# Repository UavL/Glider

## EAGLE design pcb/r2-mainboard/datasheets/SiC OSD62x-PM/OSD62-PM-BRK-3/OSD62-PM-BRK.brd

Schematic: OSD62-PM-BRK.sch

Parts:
C1, C2, C3, C6, C7, C8, C9, C10, C11, C12, C13, C14, C15, C17, C18, C19, C20, C61: 0.1uF; C0201; VOLTAGE 6.3V
C4, C62, C63: 1uF; C0402; VOLTAGE 6.3V
C5, C60: 4.7uF; C0402; VOLTAGE 10V
C16, C38, C39, C40, C42, C43, C44, C45, C51: 10uF; C0402; VOLTAGE 10V
C21, C22, C23, C41: 2.2uF; C0402; VOLTAGE 10V
C24, C26, C29, C34, C35, C36, C46, C50, C54, C55, C58: 0.1uF; C0402; VOLTAGE 6.3V
C25: 220uF; B/3528-21R
C27, C31, C32, C33, C37, C57: 10uF; C0603; VOLTAGE 10V
C28: DNP; C0402
C30: 120pF; C0402; VOLTAGE 10V
C47, C49, C53: 47uF; C0603; VOLTAGE 6.3V
C48, C52: 22uF; C0402; VOLTAGE 10V
C56: 47uF; C0805; VOLTAGE 10V
C59: 1nF; C0402; VOLTAGE 6.3V
D1: RED; EIA-STD
D2, D3, D4, D5: GREEN; EIA-STD
D6, D7: RB520S30T1G
D8: RBS2MM40C; SOD-123FL
FUD1, FUD2, FUD3, FUD4, FUD5, FUD6: FIDUCIAL; FIDUCIAL_40MIL
J1: PINHD-1X21.27; H1X2-1.27
J2, J7: PINHD-1X2; H1X2-2.54
J4: 1-1734248-5; TE_1-1734248-5
J5: USB4105-GF-A; GCT_USB4105-GF-A
J6: 2171820001; MOLEX_2171820001
J8: 505110-4091; MOLEX_505110-4091
JP1: PINHD-1X3; H1X3-2.54
JP2, JP3, JP4, JP5: PINHD-1X40; H1X40-2.54
L1, L4: 0.47uH; L0806
L2, L3: 0.47uH; L0603
R1, R3, R4, R7, R10, R11, R13, R14, R15, R16, R17, R18, R19, R20, R21, R22, R23, R24, R25, R26, R27, R28, R29, R30, R31, R32, R34, R37, R38, R39, R40, R41, R42, R43, R44, R45, R46, R47, R48, R49, R50, R51, R54, R63, R73, R76: 10k; R0402; TOLERANCE 5%
R2: 100k; R0402; TOLERANCE 5%
R5, R62: 20k; R0402; TOLERANCE 5%
R6: 100k; R0402; TOLERANCE 1%
R8: 270k; R0402; TOLERANCE 1%
R9: 180k; R0402; TOLERANCE 1%
R12, R64, R65, R66: 2k; R0402; TOLERANCE 5%
R33: 22; R0402; TOLERANCE 5%
R35, R36: 5.1K; R0402; TOLERANCE 1%
R52, R53: 4.7k; R0402; TOLERANCE 5%
R55, R56, R74: 0; R0402; TOLERANCE 5%
R57, R58, R59, R60, R61: 1k; R0402; TOLERANCE 5%
R67, R68, R69, R70: DNP; R0402; TOLERANCE 5%
R71, R72: 56K; R0402; TOLERANCE 5%
S1: MF-SW-TACT-4.2MM; TACT4.2MM
TC1: TC2050-IDC-NL
TP1, TP2, TP3, TP6, TP7: TPB0,65; TP_B0,65
U1: OSD6254-1G-IPM; OSD6254-BGA-500
U2, U9: TPD4S012_DRY_6_P1_P; DRY6
U3: TLV62595DMQR; DMQ0006A
U4: 24AA32AT-I/OT; SOT95P280X145-5N
U5: TPS22965DSGT; SON50P200X200X80-9N
U6: TPS6521903RHB; RHB0032W
U7, U8: ADC121C027CIMK; SOT95P280X110-6N
U10: TPS22918DBVR; SOT95P280X145-6N
U11: SN74LVC1G04DSFR; SON35P100X100X40-6N
U12, U13: SN74LVC2G241YZPR; YZP0008
U14: TLV75518PDQNR; DQN0004A
X1: MF-MICROSD
Y1: SIT1533AI-H4-D14-32.768; SIT1533AI_2X1.2MM
Y2: SIT8008BI-73-YYS-25.000000; QFN-4-2X1.6MM

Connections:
3V3_FB: C30.1, R6.2, R8.2, U3.3 (FB)
3V3_FB_0: R8.1, R9.2
3V3_SW: L1.1, U3.5 (SW)
ADC0_ADDR: R15.2, U7.4 (ADDR)
ADC1_ADDR: R16.1, U8.4 (ADDR)
BUCK1-0P75: C10.1, C11.1, C12.1, C13.1, C14.1, C15.1, C16.1, C53.1, L4.2, U1.G12 (VDD_CANUART), U1.G13 (VDD_CORE), U1.G14 (VDD_CORE), U1.G15 (VDD_CORE), U1.G16 (VDD_CORE), U1.H12 (VDD_CORE), U1.H13 (VDD_CORE), U1.H14 (VDD_CORE), U1.H15 (VDD_CORE), U1.H16 (VDD_CORE), U1.J12 (VDD_CORE), U1.J13 (VDD_CORE), U1.J16 (VDD_CORE), U1.K12 (VDD_CORE), U1.K13 (VDD_CORE), U1.K16 (VDD_CORE), U1.L13 (VDD_CORE), U1.L14 (VDD_CORE), U1.L15 (VDD_CORE), U1.M12 (VDDA_CORE_USB), U1.M13 (VDDA_CORE_CSIRX0), U6.1 (FB_B1)
BUCK2-1P8: C21.1, C38.1, C49.1, L3.2, U1.C15 (VMON_1P8_SOC), U6.20 (PVIN_LDO2), U6.32 (FB_B2)
BUCK3-1P2: C7.1, C8.1, C9.1, C47.1, L2.2, U1.K10 (VDDS_DDR), U1.K11 (VDDS_DDR), U1.L9 (VDDS_DDR), U1.L10 (VDDS_DDR), U1.L11 (VDDS_DDR), U1.M8 (VDDS_DDR), U1.M9 (VDDS_DDR), U1.M10 (VDDS_DDR), U1.N8 (VDDS_DDR), U1.N9 (VDDS_DDR), U6.24 (FB_B3)
CH1_LVDS_A0N: J8.11, U1.P2 (OLDI0_A0N)
CH1_LVDS_A0P: J8.12, U1.R1 (OLDI0_A0P)
CH1_LVDS_A1N: J8.14, U1.R2 (OLDI0_A1N)
CH1_LVDS_A1P: J8.15, U1.T1 (OLDI0_A1P)
CH1_LVDS_A2N: J8.20, U1.T2 (OLDI0_A2N)
CH1_LVDS_A2P: J8.21, U1.U2 (OLDI0_A2P)
CH1_LVDS_A3N: J8.23, U1.U3 (OLDI0_A3N)
CH1_LVDS_A3P: J8.24, U1.V3 (OLDI0_A3P)
CH1_LVDS_CLKN: J8.17, U1.U8 (OLDI0_CLK0N)
CH1_LVDS_CLKP: J8.18, U1.V8 (OLDI0_CLK0P)
CH2_LVDS_A0N: J8.26, U1.U4 (OLDI0_A4N)
CH2_LVDS_A0P: J8.27, U1.V4 (OLDI0_A4P)
CH2_LVDS_A1N: J8.29, U1.U5 (OLDI0_A5N)
CH2_LVDS_A1P: J8.30, U1.V5 (OLDI0_A5P)
CH2_LVDS_A2N: J8.35, U1.U6 (OLDI0_A6N)
CH2_LVDS_A2P: J8.36, U1.V6 (OLDI0_A6P)
CH2_LVDS_A3N: J8.38, U1.U7 (OLDI0_A7N)
CH2_LVDS_A3P: J8.39, U1.V7 (OLDI0_A7P)
CH2_LVDS_CLKN: J8.32, U1.U9 (OLDI0_CLK1N)
CH2_LVDS_CLKP: J8.33, U1.V9 (OLDI0_CLK1P)
CLICK0_AN: JP3.1, R56.2, U7.3 (VIN)
CLICK1_AN: JP4.40, R55.2, U8.3 (VIN)
CSI0_RXCLKN: J4.8, U1.V17 (CSI0_RXCLKN)
CSI0_RXCLKP: J4.9, U1.U17 (CSI0_RXCLKP)
CSI0_RXN0: J4.2, U1.V16 (CSI0_RXN0)
CSI0_RXN1: J4.5, U1.V15 (CSI0_RXN1)
CSI0_RXP0: J4.3, U1.U16 (CSI0_RXP0)
CSI0_RXP1: J4.6, U1.U15 (CSI0_RXP1)
EEPROM_WP: J2.2, R7.1, U4.5 (WP)
EMU0: R20.1, TC1.7, U1.D8 (EMU0)
EMU1: R21.1, TC1.10, U1.C8 (EMU1)
EXTINTN: R25.1, U1.C17 (EXTINTN), U6.11 (NINT)
EXT_REFCLK1: R56.1, U1.D16 (EXT_REFCLK1)
GND: C1.2, C2.2, C3.2, C4.2, C5.2, C6.2, C7.2, C8.2, C9.2, C10.2, C11.2, C12.2, C13.2, C14.2, C15.2, C16.2, C17.2, C18.2, C19.2, C20.2, C21.2, C22.2, C23.2, C24.2, C25.-, C26.2, C27.2, C28.2, C29.2, C31.2, C32.2, C33.2, C34.2, C35.2, C36.2, C37.2, C38.2, C39.2, C40.2, C41.2, C42.2, C43.2, C44.2, C45.2, C46.2, C47.2, C48.2, C49.2, C50.2, C51.2, C52.2, C53.2, C54.2, C55.2, C56.2, C57.2, C58.2, C59.2, C60.2, C61.2, C62.2, C63.2, D1.2 (C), D2.2 (C), D3.2 (C), D4.2 (C), D5.2 (C), J2.1, J4.1, J4.4, J4.7, J4.10, J5.A1_B12 (GND/A1/B12), J5.B1_A12 (GND/A12/B1), J5.SH1_B (SH1), J5.SH1_T (SH1), J5.SH2_B (SH2), J5.SH2_T (SH2), J5.SH3_B (SH3), J5.SH3_T (SH3), J5.SH4_B (SH4), J5.SH4_T (SH4), J6.A1 (GND), J6.A12 (GND), J6.B1 (GND), J6.B12 (GND), J6.SH_B_1 (SH1), J6.SH_B_2 (SH2), J6.SH_B_3 (SH3), J6.SH_B_4 (SH4), J6.SH_T_1 (SH1), J6.SH_T_2 (SH2), J6.SH_T_3 (SH3), J6.SH_T_4 (SH4), J8.6, J8.7, J8.10, J8.13, J8.16, J8.19, J8.22, J8.25, J8.28, J8.31, J8.34, J8.37, J8.40, J8.S1 (PAD1), J8.S2 (PAD2), JP1.1, JP2.33, JP2.40, JP3.8, JP3.33, JP4.8, JP4.33, JP5.1, JP5.30, JP5.40, R1.1, R3.1, R4.2, R6.1, R14.1, R15.1, R26.2, R27.2, R29.2, R34.2, R35.1, R36.1, R37.2, R39.2, R40.2, R41.2, R42.2, R63.2, R76.1, S1.P$3, S1.P$4, TC1.3, TC1.5, U1.A2 (VSS), U1.A14 (VSS), U1.A27 (VSS), U1.B1 (VSS), U1.B14 (VSS), U1.B28 (VSS), U1.C3 (VSS), U1.C4 (VSS), U1.C14 (VSS), U1.D3 (VSS), U1.D4 (VSS), U1.D14 (VSS), U1.E3 (VSS), U1.E4 (VSS), U1.E5 (VSS), U1.E6 (VSS), U1.E7 (VSS), U1.E8 (VSS), U1.E9 (VSS), U1.E10 (VSS), U1.E11 (VSS), U1.E12 (VSS), U1.E13 (VSS), U1.E16 (VSS), U1.E17 (VSS), U1.E18 (VSS), U1.E19 (VSS), U1.E20 (VSS), U1.E21 (VSS), U1.E22 (VSS), U1.E23 (VSS), U1.E24 (VSS), U1.F19 (VSS), U1.F20 (VSS), U1.F21 (VSS), U1.F22 (VSS), U1.F23 (VSS), U1.F24 (VSS), U1.G2 (MCU_OSC0_XO), U1.G19 (VSS), U1.G20 (VSS), U1.G23 (VSS), U1.G24 (VSS), U1.H2 (WKUP_LFOSC0_XO), U1.H19 (VSS), U1.H20 (VSS), U1.H24 (VSS), U1.J14 (VSS), U1.J15 (VSS), U1.J19 (VSS), U1.J20 (VSS), U1.J24 (VSS), U1.K6 (VSS), U1.K7 (VSS), U1.K8 (VSS), U1.K9 (VSS), U1.K14 (VSS), U1.K15 (VSS), U1.K19 (VSS), U1.K20 (VSS), U1.K24 (VSS), U1.L5 (VSS), U1.L6 (VSS), U1.L7 (VSS), U1.L8 (VSS), U1.L19 (VSS), U1.L20 (VSS), U1.L24 (VSS), U1.M4 (VSS), U1.M5 (VSS), U1.M6 (VSS), U1.M7 (VSS), U1.M20 (VSS), U1.M23 (VSS), U1.M24 (VSS), U1.N3 (VSS), U1.N4 (VSS), U1.N5 (VSS), U1.N6 (VSS), U1.N20 (VSS), U1.N21 (VSS), U1.N22 (VSS), U1.N23 (VSS), U1.N24 (VSS), U1.P3 (VSS), U1.P4 (VSS), U1.P5 (VSS), U1.P16 (VSS), U1.P17 (VSS), U1.P18 (VSS), U1.P19 (VSS), U1.P20 (VSS), U1.P21 (VSS), U1.P22 (VSS), U1.P23 (VSS), U1.P24 (VSS), U1.R3 (VSS), U1.R4 (VSS), U1.T3 (VSS), U1.T19 (VSS), U1.U1 (VSS), U1.U19 (VSS), U1.U28 (VSS), U1.V2 (VSS), U1.V19 (VSS), U1.V27 (VSS), U2.4 (GND), U3.4 (GND), U4.2 (VSS), U5.5 (GND), U5.9 (EXP), U6.15 (AGND), U6.PAD, U7.2 (GND), U8.2 (GND), U9.4 (GND), U10.2 (GND), U11.3 (GND), U12.A1 (1OEN), U12.D1 (GND), U13.A1 (1OEN), U13.D1 (GND), U14.2 (GND), U14.5 (EP), X1.G0 (GND), X1.G1 (GND), X1.PIN6 (VSS), Y1.2 (GND), Y2.2 (GND)
GPMC0_AD0: JP5.39, R51.1, U1.G28 (GPMC0_AD0)
GPMC0_AD1: JP5.38, R49.1, U1.G27 (GPMC0_AD1)
GPMC0_AD2: JP5.37, R42.1, U1.F28 (GPMC0_AD2)
GPMC0_AD3: JP5.36, R41.1, U1.F27 (GPMC0_AD3)
GPMC0_AD4: JP5.35, R40.1, U1.E28 (GPMC0_AD4)
GPMC0_AD5: JP5.34, R39.1, U1.E27 (GPMC0_AD5)
GPMC0_AD6: JP5.33, R38.1, U1.D28 (GPMC0_AD6)
GPMC0_AD7: JP5.32, R37.1, U1.D27 (GPMC0_AD7)
GPMC0_AD8: JP2.29, R34.1, U1.L27 (GPMC0_AD8)
GPMC0_AD9: JP3.29, R32.1, U1.L28 (GPMC0_AD9)
GPMC0_AD10: JP2.30, R31.1, U1.K27 (GPMC0_AD10)
GPMC0_AD11: JP3.30, R30.1, U1.K28 (GPMC0_AD11)
GPMC0_AD12: JP2.31, R29.1, U1.J28 (GPMC0_AD12)
GPMC0_AD13: JP3.31, R28.1, U1.J27 (GPMC0_AD13)
GPMC0_AD14: JP2.32, R27.1, U1.H28 (GPMC0_AD14)
GPMC0_AD15: JP3.32, R26.1, U1.H27 (GPMC0_AD15)
GPMC0_ADVN_ALE: JP4.31, U1.H25 (GPMC0_ADVN_ALE)
GPMC0_BE0N_CLE: JP2.38, U1.J26 (GPMC0_BE0N_CLE)
GPMC0_BE1N: JP2.36, U1.K25 (GPMC0_BE1N)
GPMC0_CLK: JP2.37, U1.K26 (GPMC0_CLK)
GPMC0_CSN0: JP4.29, U1.F26 (GPMC0_CSN0)
GPMC0_CSN1: JP5.29, U1.F25 (GPMC0_CSN1)
GPMC0_CSN2: JP4.28, U1.E26 (GPMC0_CSN2)
GPMC0_CSN3: JP5.28, U1.E25 (GPMC0_CSN3)
GPMC0_DIR: JP4.30, U1.G25 (GPMC0_DIR)
GPMC0_OEN_REN: JP4.32, U1.H26 (GPMC0_OEN_REN)
GPMC0_WAIT0: JP2.34, U1.L25 (GPMC0_WAIT0)
GPMC0_WAIT1: JP2.35, U1.L26 (GPMC0_WAIT1)
GPMC0_WEN: JP2.39, U1.J25 (GPMC0_WEN)
GPMC0_WPN: JP5.31, U1.G26 (GPMC0_WPN)
I2C0_SCL: J7.2, J8.2, R52.1, U1.A12 (I2C0_SCL), U4.1 (SCL), U6.10 (SCL), U7.5 (SCL), U8.5 (SCL)
I2C0_SDA: J7.1, J8.3, R53.1, U1.B12 (I2C0_SDA), U4.3 (SDA), U6.9 (SDA), U7.6 (SDA), U8.6 (SDA)
I2C1_SCL: JP3.36, R69.1, U1.A13 (I2C1_SCL)
I2C1_SDA: JP3.35, R70.1, U1.B13 (I2C1_SDA)
LDO1-1P8-3P3: C23.1, C42.1, R43.2, R44.2, R45.2, R46.2, R47.2, U1.G21 (VDDSHV5), U1.G22 (VDDSHV5), U6.7 (VLDO1)
LDO2-0P85: C17.1, C18.1, C19.1, C43.1, U1.H17 (VDDR_CORE), U1.H18 (VDDR_CORE), U1.J17 (VDDR_CORE), U1.J18 (VDDR_CORE), U1.K17 (VDDR_CORE), U1.K18 (VDDR_CORE), U1.L17 (VDDR_CORE), U1.L18 (VDDR_CORE), U6.19 (VLDO2)
LDO3-1P8: C1.1, C2.1, C3.1, C4.1, C5.1, C44.1, C46.1, C54.1, R24.2, R50.1, U1.D15 (VDDS_OSC0), U1.F13 (VDDA_MCU), U1.F14 (VDDA_PLL2), U1.N12 (VDDA_TEMP), U1.N13 (VDDA_PLL0), U1.N14 (VDDA_PLL1), U1.P11 (VDDA_1P8_OLDI0), U1.P12 (VDDA_1P8_USB), U1.P13 (VDDA_1P8_CSIRX0), U6.21 (VLDO3), Y1.4 (VDD), Y2.4 (VDD)
LDO4-2P5: C20.1, C45.1, U1.N10 (DDR_VPP), U6.23 (VLDO4)
LED1: D1.1 (A), R57.1
LED2: D2.1 (A), R58.1
LED3: D3.1 (A), R59.1
LED4: D4.1 (A), R60.1
LED5: D5.1 (A), R61.1
LX_B1: L4.1, U6.2 (LX_B1_1), U6.3 (LX_B1_2)
LX_B2: L3.1, U6.29 (LX_B2)
LX_B3: L2.1, U6.27 (LX_B3)
MCAN0_RX: JP3.37, U1.A11 (MCAN0_RX)
MCAN0_TX: JP3.38, U1.B11 (MCAN0_TX)
MCASP0_ACLKR: JP3.39, U1.B19 (MCASP0_ACLKR)
MCASP0_ACLKX: R58.2, U1.A18 (MCASP0_ACLKX)
MCASP0_AFSR: JP3.40, U1.A19 (MCASP0_AFSR)
MCASP0_AFSX: R59.2, U1.B18 (MCASP0_AFSX)
MCASP0_AXR0: R60.2, U1.B17 (MCASP0_AXR0)
MCASP0_AXR1: R61.2, U1.A17 (MCASP0_AXR1)
MCASP0_AXR2: JP4.39, U1.B16 (MCASP0_AXR2)
MCASP0_AXR3: R55.1, U1.A16 (MCASP0_AXR3)
MCU_ERRORN: TP2.TP, U1.D7 (MCU_ERRORN)
MCU_I2C0_SCL: JP5.14, R65.1, U1.A7 (MCU_I2C0_SCL)
MCU_I2C0_SDA: JP4.14, R66.1, U1.B7 (MCU_I2C0_SDA)
MCU_MCAN0_RX: JP5.4, U1.E1 (MCU_MCAN0_RX)
MCU_MCAN0_TX: JP5.5, U1.E2 (MCU_MCAN0_TX)
MCU_MCAN1_RX: JP5.2, U1.F1 (MCU_MCAN1_RX)
MCU_MCAN1_TX: JP5.3, U1.F2 (MCU_MCAN1_TX)
MCU_OSC0_XI: U1.G1 (MCU_OSC0_XI), Y2.3 (OUT)
MCU_PORZ: JP4.15, R24.1, U1.D6 (MCU_PORZ), U6.18 (NRSTOUT)
MCU_RESETSTATZ: TP3.TP, U1.C6 (MCU_RESETSTATZ)
MCU_RESETZ: R10.1, U1.C5 (MCU_RESETZ)
MCU_SPI0_CLK: JP4.11, U1.A4 (MCU_SPI0_CLK)
MCU_SPI0_CS0: JP5.13, U1.B6 (MCU_SPI0_CS0)
MCU_SPI0_CS1: JP4.13, U1.A6 (MCU_SPI0_CS1)
MCU_SPI0_D0: JP5.12, U1.B5 (MCU_SPI0_D0)
MCU_SPI0_D1: JP4.12, U1.A5 (MCU_SPI0_D1)
MCU_UART0_CTSN: JP5.11, U1.B4 (MCU_UART0_CTSN)
MCU_UART0_RTSN: JP4.10, U1.A3 (MCU_UART0_RTSN)
MCU_UART0_RXD: JP4.9, U1.B2 (MCU_UART0_RXD)
MCU_UART0_TXD: JP5.10, U1.B3 (MCU_UART0_TXD)
MDIO0_MDC: JP3.12, U1.V26 (MDIO0_MDC)
MDIO0_MDIO: JP2.12, U1.U26 (MDIO0_MDIO)
MMC0_CLK: JP4.5, R67.1, U1.J1 (MMC0_CLK)
MMC0_CMD: JP4.6, R68.1, U1.K1 (MMC0_CMD)
MMC0_DAT0: JP3.4, U1.K2 (MMC0_DAT0)
MMC0_DAT1: JP3.3, U1.L1 (MMC0_DAT1)
MMC0_DAT2: JP4.1, U1.L2 (MMC0_DAT2)
MMC0_DAT3: JP4.2, U1.M1 (MMC0_DAT3)
MMC0_DAT4: JP3.6, U1.M2 (MMC0_DAT4)
MMC0_DAT5: JP3.5, U1.N1 (MMC0_DAT5)
MMC0_DAT6: JP4.4, U1.N2 (MMC0_DAT6)
MMC0_DAT7: JP4.3, U1.P1 (MMC0_DAT7)
MMC1_CLK: R33.2, U1.B21 (MMC1_CLK)
MMC1_CLK_R: R33.1, X1.PIN5 (CLK)
MMC1_CMD: R45.1, U1.A21 (MMC1_CMD), X1.PIN3 (CMD)
MMC1_DAT0: R46.1, U1.A22 (MMC1_DAT0), X1.PIN7 (DAT0)
MMC1_DAT1: R47.1, U1.B22 (MMC1_DAT1), X1.PIN8 (DAT1)
MMC1_DAT2: R43.1, U1.A20 (MMC1_DAT2), X1.PIN1 (DAT2)
MMC1_DAT3: R44.1, U1.B20 (MMC1_DAT3), X1.PIN2 (CD/DAT3)
MMC1_SDCD: U1.A23 (MMC1_SDCD), U11.4 (Y)
MMC1_SDWP: R13.1, U1.B23 (MMC1_SDWP), U6.12 (VSEL_SD/VSEL_DDR)
MMC2_CLK: JP4.20, U1.D23 (MMC2_CLK)
MMC2_CMD: JP5.20, U1.C23 (MMC2_CMD)
MMC2_DAT0: JP5.19, U1.D22 (MMC2_DAT0)
MMC2_DAT1: JP4.19, U1.C22 (MMC2_DAT1)
MMC2_DAT2: JP5.18, U1.D21 (MMC2_DAT2)
MMC2_DAT3: JP4.18, U1.C21 (MMC2_DAT3)
MMC2_SDCD: JP5.17, U1.D20 (MMC2_SDCD)
MMC2_SDWP: JP4.17, U1.C20 (MMC2_SDWP)
MPU_HFOSC_EN: R50.2, Y2.1 (ST)
OSPI0_CLK: JP4.23, U1.A24 (OSPI0_CLK)
OSPI0_CSN0: JP4.22, U1.D25 (OSPI0_CSN0)
OSPI0_CSN1: D7.CATHODE (C), U1.C25 (OSPI0_CSN1)
OSPI0_CSN2: JP4.21, U1.D24 (OSPI0_CSN2)
OSPI0_CSN3: JP5.21, U1.C24 (OSPI0_CSN3)
OSPI0_D0: JP5.24, U1.B24 (OSPI0_D0)
OSPI0_D1: JP4.24, U1.A25 (OSPI0_D1)
OSPI0_D2: JP5.25, U1.B25 (OSPI0_D2)
OSPI0_D3: JP4.25, U1.A26 (OSPI0_D3)
OSPI0_D4: JP5.26, U1.B26 (OSPI0_D4)
OSPI0_D5: JP4.26, U1.B27 (OSPI0_D5)
OSPI0_D6: JP5.27, U1.C27 (OSPI0_D6)
OSPI0_D7: JP4.27, U1.C28 (OSPI0_D7)
OSPI0_DQS: JP5.23, U1.D26 (OSPI0_DQS)
OSPI0_LBCLKO: JP5.22, R74.2, U1.C26 (OSPI0_LBCLKO)
OSPI0_LBCLKO_R: J1.1, R74.1, U13.C1 (2Y)
PMIC_LPM_EN0: R23.1, U1.D5 (PMIC_LPM_EN0), U6.31 (MODE_STBY)
PMIC_PWR_BTN: R22.1, S1.P$1, S1.P$2, U6.25 (EN/PB/VSENSE)
PORZ_OUT: TP1.TP, U1.D18 (PORZ_OUT)
RESETSTATZ: D6.CATHODE (C), U1.C18 (RESETSTATZ), U6.28 (MODE_RESET), U13.B1 (1A)
RESET_REQZ: R11.1, U1.D17 (RESET_REQZ)
RGMII1_RD0: JP2.8, U1.U22 (RGMII1_RD0)
RGMII1_RD1: JP2.7, U1.V22 (RGMII1_RD1)
RGMII1_RD2: JP2.6, U1.U21 (RGMII1_RD2)
RGMII1_RD3: JP2.5, U1.V21 (RGMII1_RD3)
RGMII1_RXC: JP2.4, U1.U20 (RGMII1_RXC)
RGMII1_RX_CTL: JP2.3, U1.V20 (RGMII1_RX_CTL)
RGMII1_TD0: JP2.11, U1.U25 (RGMII1_TD0)
RGMII1_TD1: JP3.11, U1.V25 (RGMII1_TD1)
RGMII1_TD2: JP2.10, U1.U24 (RGMII1_TD2)
RGMII1_TD3: JP3.10, U1.V24 (RGMII1_TD3)
RGMII1_TXC: JP2.9, U1.U23 (RGMII1_TXC)
RGMII1_TX_CTL: JP3.9, U1.V23 (RGMII1_TX_CTL)
RGMII2_RD0: JP2.18, U1.T25 (RGMII2_RD0)
RGMII2_RD1: JP3.18, U1.R24 (RGMII2_RD1)
RGMII2_RD2: JP2.17, U1.T24 (RGMII2_RD2)
RGMII2_RD3: JP3.17, U1.R23 (RGMII2_RD3)
RGMII2_RXC: JP3.16, U1.R22 (RGMII2_RXC)
RGMII2_RX_CTL: JP2.16, U1.T23 (RGMII2_RX_CTL)
RGMII2_TD0: JP2.15, U1.T22 (RGMII2_TD0)
RGMII2_TD1: JP3.15, U1.R21 (RGMII2_TD1)
RGMII2_TD2: JP2.14, U1.T21 (RGMII2_TD2)
RGMII2_TD3: JP3.14, U1.R20 (RGMII2_TD3)
RGMII2_TXC: JP3.13, U1.R19 (RGMII2_TXC)
RGMII2_TX_CTL: JP2.13, U1.T20 (RGMII2_TX_CTL)
RXD: JP1.2, R76.2, U12.B1 (1A)
SDCD_INV: R48.1, U11.2 (A), X1.PIN9 (DET), X1.PIN10 (DET)
SD_LS_ON: D6.ANODE (A), D7.ANODE (A), R54.2, U10.3 (ON)
SPI0_CLK: JP4.37, U1.C11 (SPI0_CLK)
SPI0_CS0: JP4.38, U1.D13 (SPI0_CS0)
SPI0_CS1: JP3.2, U1.C13 (SPI0_CS1)
SPI0_D0: JP4.36, U1.D12 (SPI0_D0)
SPI0_D1: JP4.35, U1.C12 (SPI0_D1)
TCK: R19.1, TC1.4, U1.D9 (TCK)
TDI: R17.1, TC1.8, U1.D10 (TDI)
TDO: TC1.6, U1.D11 (TDO)
TMS: R18.1, TC1.2, U1.C10 (TMS)
TPS22965_CT: C28.1, U5.6 (CT)
TPS22965_EN: R73.1, U5.3 (ON), U6.17 (GPO2)
TRSTN: R14.2, TC1.9, U1.C9 (TRSTN)
TS_INT#: J8.9, TP7.TP, U13.D2 (2A)
TS_RESET_N: J8.8, TP6.TP, U13.C2 (1Y)
TXD: JP1.3, U12.C1 (2Y)
UART0_CTSN: JP4.16, U1.A9 (UART0_CTSN)
UART0_RTSN: JP5.16, U1.B9 (UART0_RTSN)
UART0_RXD: U1.A10 (UART0_RXD), U12.C2 (1Y)
UART0_TXD: U1.B10 (UART0_TXD), U12.D2 (2A)
USB0_CC1: J5.A5 (CC1), R35.2
USB0_CC2: J5.B5 (CC2), R36.2
USB0_DM: J5.A7 (DN1), J5.B7 (DN2), U1.U12 (USB0_DM), U9.2 (D-)
USB0_DP: J5.A6 (DP1), J5.B6 (DP2), U1.V12 (USB0_DP), U9.1 (D+)
USB0_DRVVBUS: J4.11, U1.C19 (USB0_DRVVBUS)
USB0_VBUS: R62.1, R63.1, U1.V11 (USB0_VBUS)
USB1_CC1: J6.A5 (CC1), R72.1
USB1_CC2: J6.B5 (CC2), R71.1
USB1_DM: J6.A7 (DN1), J6.B7 (DN2), U1.U10 (USB1_DM), U2.2 (D-)
USB1_DP: J6.A6 (DP1), J6.B6 (DP2), U1.V10 (USB1_DP), U2.1 (D+)
USB1_DRVVBUS: J4.12, U1.D19 (USB1_DRVVBUS)
USB1_VBUS: R4.1, R5.1, U1.U11 (USB1_VBUS)
VBUS: C50.1, C60.1, D8.A, J5.A4_B9 (VBUS/A4/B9), J5.B4_A9 (VBUS/A9/B4), U9.6 (VBUS)
VDD1P8_CAP: C41.1, U6.14 (VDD1P8)
VDD_SD: C57.1, C58.1, U10.5 (QOD), U10.6 (VOUT), X1.PIN4 (VDD)
VIN-3P3: C30.2, C31.1, C32.1, C33.1, C39.1, C40.1, C48.1, C51.1, C52.1, L1.2, R9.1, R22.2, R73.2, U5.1 (VIN), U5.2 (VIN), U5.4 (VBIAS), U6.4 (PVIN_B1_1), U6.5 (PVIN_B1_2), U6.6 (PVIN_LDO1), U6.13 (VSYS), U6.22 (PVIN_LDO34), U6.26 (PVIN_B3), U6.30 (PVIN_B2)
VIN-3P3-LS: C6.1, C22.1, C26.1, C29.1, C34.1, C35.1, C36.1, C37.1, C61.1, C63.1, J4.15, J8.1, JP2.2, JP3.7, JP4.34, R7.2, R10.2, R11.2, R12.2, R13.2, R16.2, R17.2, R18.2, R19.2, R20.2, R21.2, R23.2, R25.2, R28.2, R30.2, R31.2, R32.2, R38.2, R48.2, R49.2, R51.2, R52.2, R53.2, R54.1, R57.2, R64.2, R65.2, R66.2, R67.2, R68.2, R69.2, R70.2, TC1.1, U1.B15 (VMON_3P3_SOC), U1.F11 (VDDSHV_CANUART), U1.F12 (VDDSHV_MCU), U1.G10 (VDDSHV_CANUART), U1.G11 (VDDSHV_MCU), U1.H21 (VDDSHV6), U1.H22 (VDDSHV6), U1.J21 (VDDSHV0), U1.J22 (VDDSHV0), U1.K21 (VDDSHV1), U1.K22 (VDDSHV1), U1.L21 (VDDSHV3), U1.L22 (VDDSHV3), U1.M21 (VDDSHV2), U1.M22 (VDDSHV2), U1.N7 (VDDA_3P3_USB), U1.N11 (VDDSHV4), U1.P10 (VDDSHV4), U4.4 (VCC), U5.7 (VOUT), U5.8 (VOUT), U7.1 (VA), U8.1 (VA), U10.1 (VIN), U11.6 (VCC), U12.A2 (VCC), U12.B2 (2OE), U13.A2 (VCC), U13.B2 (2OE), U14.4 (IN)
VIN-5P0: C24.1, C25.+, C27.1, C55.1, C56.1, C59.1, D8.C, J6.A4 (VBUS), J6.A9 (VBUS), J6.B4 (VBUS), J6.B9 (VBUS), JP2.1, JP3.34, JP4.7, R2.2, R5.2, R62.2, R71.2, R72.2, U2.6 (VBUS), U3.1 (EN), U3.6 (VIN)
VMON_ER_SYS: R1.2, R2.1, U1.A15 (VMON_VSYS)
VOUT0_DATA0: JP2.21, U1.P26 (VOUT0_DATA0)
VOUT0_DATA1: JP3.21, U1.N25 (VOUT0_DATA1)
VOUT0_DATA2: JP2.22, U1.N26 (VOUT0_DATA2)
VOUT0_DATA3: JP3.22, U1.M25 (VOUT0_DATA3)
VOUT0_DATA4: JP2.23, U1.M26 (VOUT0_DATA4)
VOUT0_DATA5: JP3.23, U1.U27 (VOUT0_DATA5)
VOUT0_DATA6: JP2.24, U1.T27 (VOUT0_DATA6)
VOUT0_DATA7: JP3.24, U1.T28 (VOUT0_DATA7)
VOUT0_DATA8: JP2.25, U1.R27 (VOUT0_DATA8)
VOUT0_DATA9: JP3.25, U1.R28 (VOUT0_DATA9)
VOUT0_DATA10: JP2.26, U1.P27 (VOUT0_DATA10)
VOUT0_DATA11: JP3.26, U1.P28 (VOUT0_DATA11)
VOUT0_DATA12: JP2.27, U1.N27 (VOUT0_DATA12)
VOUT0_DATA13: JP3.27, U1.N28 (VOUT0_DATA13)
VOUT0_DATA14: JP2.28, U1.M27 (VOUT0_DATA14)
VOUT0_DATA15: JP3.28, U1.M28 (VOUT0_DATA15)
VOUT0_DE: JP2.19, U1.R25 (VOUT0_DE)
VOUT0_HSYNC: JP3.20, U1.P25 (VOUT0_HSYNC)
VOUT0_PCLK: JP3.19, U1.T26 (VOUT0_PCLK)
VOUT0_VSYNC: JP2.20, U1.R26 (VOUT0_VSYNC)
VPP: C62.1, U1.C16 (VPP), U14.1 (OUT)
VPP_EN: J1.2, R3.2, U14.3 (EN)
WKUP_CLKOUT0: JP5.15, U1.C7 (WKUP_CLKOUT0)
WKUP_I2C0_SCL: J4.13, R64.1, U1.A8 (WKUP_I2C0_SCL)
WKUP_I2C0_SDA: J4.14, R12.1, U1.B8 (WKUP_I2C0_SDA)
WKUP_LFOSC0_XI: U1.H1 (WKUP_LFOSC0_XI), Y1.3 (OUT)
WKUP_UART0_CTSN: JP5.6, U1.D1 (WKUP_UART0_CTSN)
WKUP_UART0_RTSN: JP5.7, U1.D2 (WKUP_UART0_RTSN)
WKUP_UART0_RXD: JP5.9, U1.C2 (WKUP_UART0_RXD)
WKUP_UART0_TXD: JP5.8, U1.C1 (WKUP_UART0_TXD)

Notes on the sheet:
OSD62-PM BRK
Version 1D
Table of Contents
Sheet 1: Title
Sheet 2: Notes / Block Diagram / Mechanical
Sheet 3: OSD62-PM Power
Sheet 4: OSD62-PM GND / IO Power
Sheet 5: OSD62-PM Signals
Sheet 6: USB-C / CSI / Power In / Osc
Sheet 7: Power Management
Sheet 8: JTAG / Boot Mode / microSD / etc.
1/12
2/12
8/12
9/12
11/12
6/12
12/12
Sheet 9: IO Headers
Sheet 12: Design Notes
MicroSD
JTAG Headers
Design Notes
Revision 1A - Intial Revision - Pre-Production Revision 1B - Fixed issue with USB connector shorting power and ground - Updated SD card connections to fix UHS-I speed transition - Updated PC / PD headers Revision 1C - Added inverter on microSD card CD pin - Added back current protection for USB-C U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
Mechanical & Misc
Boot Modes Decode: 1, PLL Config B[2:0] = 0b011 : Ref Clock = 25MHz 2, Primary Boot B[9:3] = 0b1001000 : SDCard FS Boot 3, Backup Boot B[13:10] = 0b1011 : UART Boot
Fiducials
UART Header
USB-C Connector
IO Headers
Note: VDDSHV5 is used for this interface. LDO1 from the PMIC supports both 1.8V and 3.3V operation to support SD3.0 speed
Power Management
OSD62-PM Power
OSD62-PM Signals
Oscillators
OSD62-PM Ground
VDD_CORE
VDD_CANUART
VDDR_CORE
VDDA_1P8_OLDI0

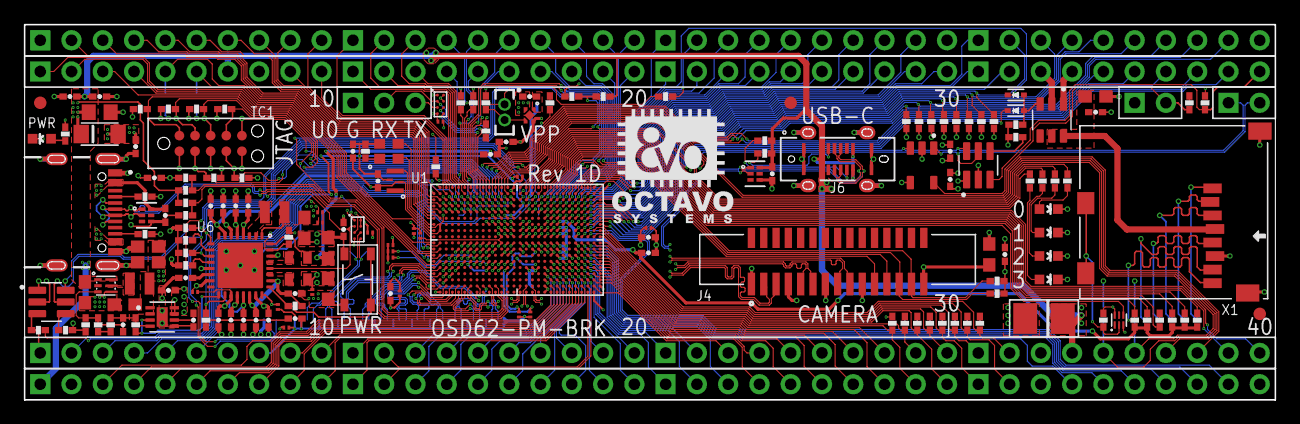
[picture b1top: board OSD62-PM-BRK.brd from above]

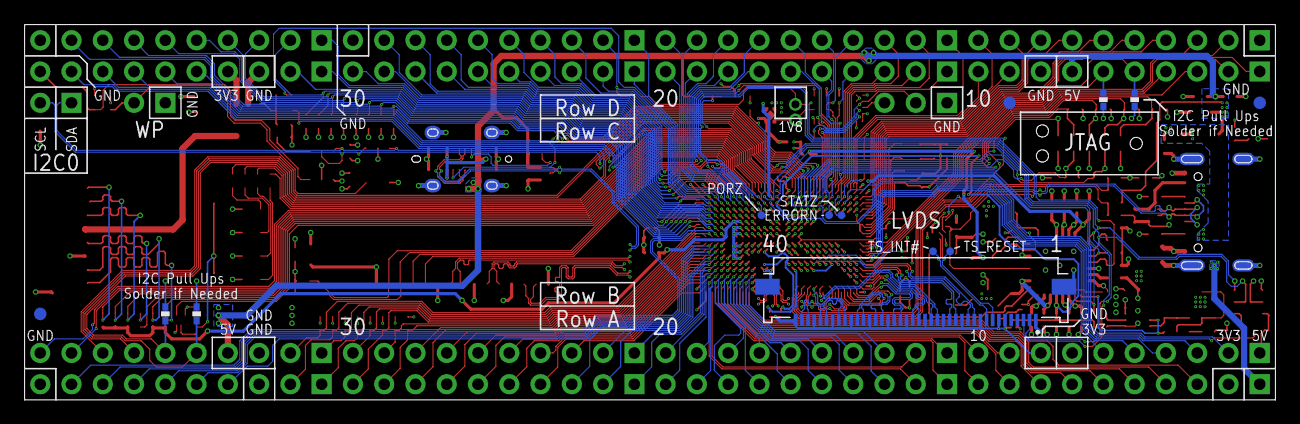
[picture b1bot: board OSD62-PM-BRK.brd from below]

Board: 4 copper layers, 101.6 x 30.5 mm, 194 parts (13 on the bottom side), 264 nets.

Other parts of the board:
U$1: OCTAVO-LOGO-8VO
U$2: OCTAVO-LOGO-WORDS-SMALL

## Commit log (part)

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2025-10-16 Fix description about VCOM settings
2025-10-16 Skip empty lines when dumping wbf
2025-10-16 Update for new boards; Force reset when lost of signal
2025-11-23 Implement blanking and power-off
2025-11-24 Fix tick time calculation
2025-12-07 add the hash for current Git head to the 'ver' shell command
2025-12-15 Add provision for supporting touchscreen
2026-01-26 Disable VCOM when powering off
2026-01-26 Use absolute path for submodule
2026-02-27 Fix reboot loop when input source is not auto
2026-02-28 Update flash tool
2026-03-03 Update waveform tools to support multi-voltage panels
2026-05-09 add state tracking for PTN3460 to avoid race condition
    This fixes a bug where the USB PD task may try to send i2c commands to
    PTN3460 after it's being shut down, which causes fw to lock up
2026-05-10 add a few new filesystem commands scoped under 'fs'
    Some of the existing commands such as 'dump' and 'format' are also moved
    under the 'fs' umbrella for consistency and to reduce clutter at the
    top level
2026-05-10 add support for configuring custom bistream file names
    The code is backward compatible with existing config files.
2026-05-10 extend memory related info to show stats for heap as well
    The new 'mem [detail]' command shows the info from previous 'stacks'
    command and adds heap allocation stats.
2026-05-10 add compiler config for building run-from-RAM debug fw
    * DebugRAM build configuration is added in STM32CubeIDE. The default is
    still 'Debug', so the new config must be intentionally selected when
    building the firmware. The differences from the 'Debug' config are:
    * using STM32H750VBTX_RAM.ld linker script instead of _FLASH.ld
    * define USER_VECT_TAB_ADDRESS and VECT_TAB_SRAM; as far as I
    understand, this way the interrupt vectors table is placed in RAM
2026-06-28 Implement native low-power standby mode and DisplayPort wakeup

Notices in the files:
pcb/r2-mainboard/datasheets/SiC OSD62x-PM/OSD62-PM-BRK-3/OSD62-PM-BRK.sch:
(c) Copyright, Octavo Systems LLC, 2024-2025. All Rights Reserved.
